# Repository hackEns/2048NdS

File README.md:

Nuit des Sciences 2014
======================

Codes, schematics etc. pour l'installation de LEDs (montage Ledhill) pour la Nuit des Sciences 2014 à l'Ens.

# Structure

* `frontend/`: web interface for playing, customized 2048 game to be used as a controller for the game server.
* `leds/`: code running on the ATmega on the LEDs PCB.
* `pc_control/`: python scripts to send instructions to the LEDs.
* `tests/`: various tests files for both the PCBs and the Serial comm in Python.

# Usage

* Launch `test_order.py` in the `tests` folder, to get the correct order in which LEDs should be controlled.
* Put the output of the previous command in the `get_linear_led_number` function in `pc_control/game.py` line 98 to set the correct order for the LEDs.
* Set the correct controller at the top of `pc_control/game.py`.
* Launch `leds_server.py` in the `pc_control` folder, on the computer connected to the LEDs using a USB FTDI cable. Pass the device `/dev/ttyUSB*` used to communicate with the LEDs as argument.
* Launch `game.py` in the `pc_control` folder passing it the server ip address as first argument. This can be launched on any computer as long as it can communicate with the previous one _via_ the port 4242 (or any other port, if you update the files `game.py` and `leds_server.py` accordingly).
* You are ready to go.

# License

All the source codes, unless explicitly specified otherwise are under the following license:

```
/*
 * --------------------------------------------------------------------------------
 * "THE NO-ALCOHOL BEER-WARE LICENSE" (Revision 42):
 * Phyks (webmaster@phyks.me) wrote or updated these files for hackEns. As long
 * as you retain this notice you can do whatever you want with this stuff
 * (and you can also do whatever you want with this stuff without retaining it,
 * but that's not cool...).
 *
 * If we meet some day, and you think this stuff is worth it, you can buy us a
 * <del>beer</del> soda in return.
 *                                                              Phyks for hackEns
 * ---------------------------------------------------------------------------------
 */
 ```

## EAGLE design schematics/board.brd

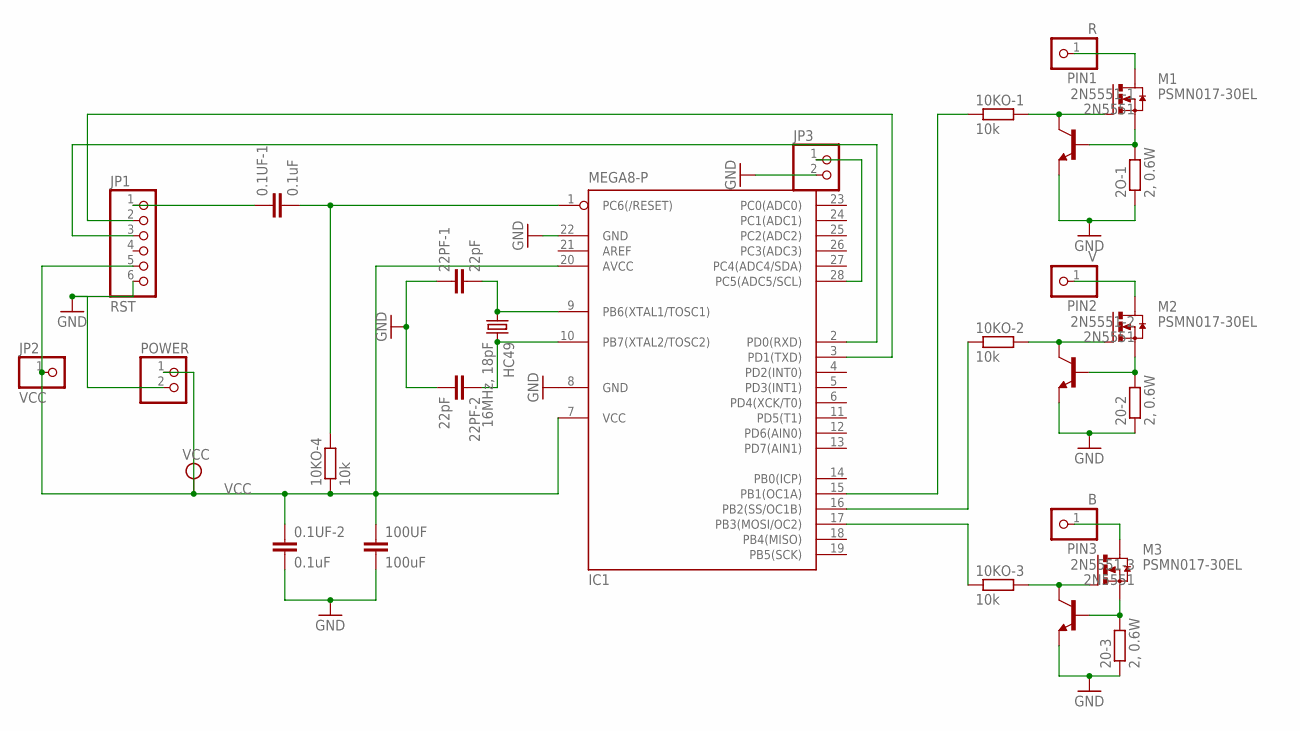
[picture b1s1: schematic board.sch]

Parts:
0.1UF-1, 0.1UF-2: 0.1uF; C025-030X050
2N5551-1, 2N5551-2, 2N5551-3: 2N5551; TO92-CBE
2O-1, 20-2, 20-3: 2, 0.6W; 0309V
10KO-1, 10KO-2, 10KO-3, 10KO-4: 10k; 0207/2V
22PF-1, 22PF-2: 22pF; C025-030X050
100UF: 100uF; C025-050X050
HC49: 16MHz, 18pF; HC49/S
IC1: MEGA8-P; DIL28-3
JP1: RST; 1X06
JP2: VCC; 1X01
JP3: PINHD-1X2; 1X02
M1, M2, M3: PSMN017-30EL; TO262-V
PIN1: R; 1X01
PIN2: V; 1X01
PIN3: B; 1X01
POWER: PINHD-1X2; 1X02

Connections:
GND: 0.1UF-2.2, 2N5551-1.E, 2N5551-2.E, 2N5551-3.E, 2O-1.1, 20-2.1, 20-3.1, 22PF-1.1, 22PF-2.2, 100UF.2, IC1.8 (GND), IC1.22 (GND), JP1.6, JP3.2, POWER.2
unnamed: 22PF-1.2, HC49.1, IC1.9 (PB6(XTAL1/TOSC1))
unnamed: 22PF-2.1, HC49.2, IC1.10 (PB7(XTAL2/TOSC2))
unnamed: 0.1UF-1.1, JP1.1
unnamed: 2N5551-2.C, 10KO-2.2, M2.1 (G)
unnamed: 0.1UF-1.2, 10KO-4.2, IC1.1 (PC6(/RESET))
unnamed: 2N5551-1.C, 10KO-1.2, M1.1 (G)
unnamed: 2N5551-2.B, 20-2.2, M2.3 (S)
unnamed: 2N5551-1.B, 2O-1.2, M1.3 (S)
unnamed: IC1.3 (PD1(TXD)), JP1.2
unnamed: 2N5551-3.C, 10KO-3.2, M3.1 (G)
unnamed: 2N5551-3.B, 20-3.2, M3.3 (S)
unnamed: IC1.2 (PD0(RXD)), JP1.3
unnamed: 10KO-1.1, IC1.15 (PB1(OC1A))
unnamed: 10KO-2.1, IC1.16 (PB2(SS/OC1B))
unnamed: 10KO-3.1, IC1.17 (PB3(MOSI/OC2))
unnamed: M1.2 (D), PIN1.1
unnamed: M2.2 (D), PIN2.1
unnamed: M3.2 (D), PIN3.1
unnamed: IC1.28 (PC5(ADC5/SCL)), JP3.1
VCC: 0.1UF-2.1, 10KO-4.1, 100UF.1, IC1.7 (VCC), IC1.20 (AVCC), JP1.5, JP2.1, POWER.1

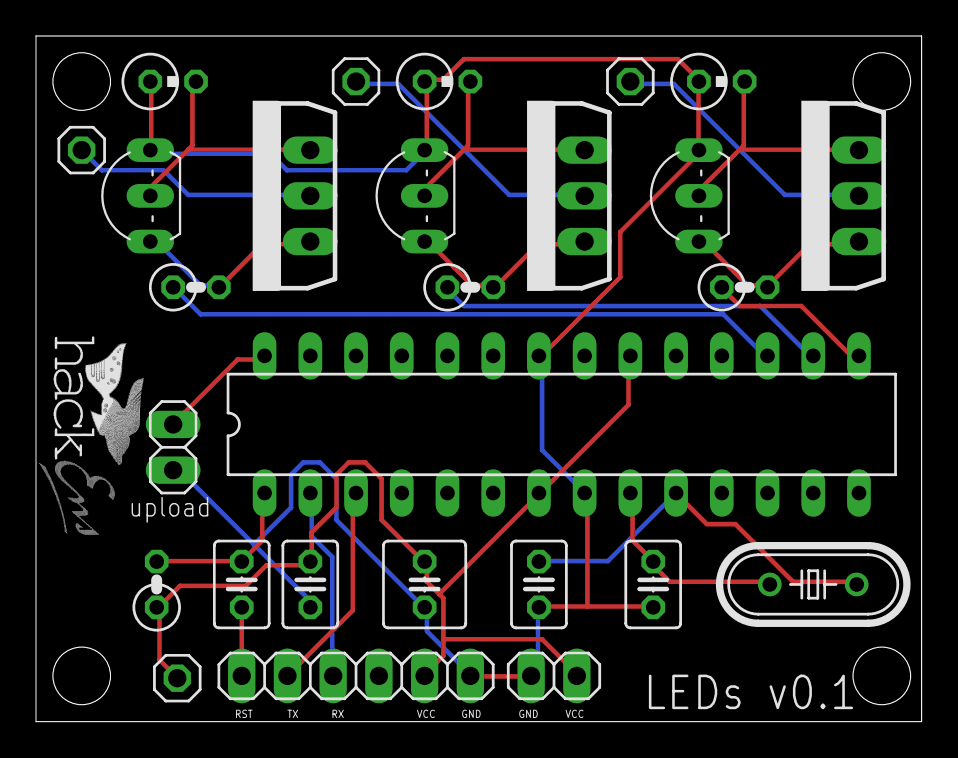
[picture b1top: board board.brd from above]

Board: 2 copper layers, 49.2 x 38.1 mm, 28 parts (0 on the bottom side), 21 nets.

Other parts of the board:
U$1: HACKENS-LOGO

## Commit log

2014-05-19 3x3 + updated layout
2014-05-19 Updated license
2014-05-19 Cleaned repo
2014-05-20 * Code des LEDs * Début du code de contrôle
2014-05-20 Control class
2014-05-22 LED control
2014-05-22 README
2014-05-22 2048 board class
2014-05-22 Complete structure
2014-05-24 LED server should be ok
    Code is composed of two modules :
    * A LED server which receive instructions and forward them to the LEDs
    * A game server which handles the gaming and sends instructions
    accordingly to the LED server.
2014-05-24 Updating game server
2014-05-25 Game server + high scores
2014-05-25 Game server + LED server improved
    * Bugfixes
    TODO : get_diff not working + error in send_colors
2014-05-25 LED server working
2014-05-25 Game working
2014-05-25 README, doc and LICENSE
2014-05-26 README + License
2014-05-26 PEP8 + requests error handling
2014-05-27 Web controller
2014-05-27 Frontend web controller
2014-05-27 Web controller working
2014-05-29 More robust webcontroller
2014-05-29 Controller for the accelerometer app on smartphone
2014-06-02 Default port pour acceleromètre
2014-06-02 Added predefined colors
2014-06-02 Basic visualizer to test anims
2014-06-02 Created a static code for the LED on 45 rue d'Ulm
2014-06-02 Readability
2014-06-03 Visualizer updated
2014-06-03 No threading to respect timing
2014-06-03 Win and lose animations
2014-06-05 Typo in colors
2014-06-05 Animations pour les LEDs du 45
2014-06-05 Animations 45 testées
2014-06-05 Update colors
2014-06-05 Bugfixes
2014-06-05 Bugfix in static leds code
2014-06-05 Bugfix in 45 + test_correction
2014-06-05 Bugfix in test serial
2014-06-05 Rebug fix in test_serial
2014-06-06 Script pour corriger les LEDs
2014-06-06 Position updated
2014-06-06 Bugfix in game
2014-06-06 Updated corrections for the LEDs
2014-06-06 Port 22, port 4242 blocked
2014-06-06 User friendly game.py for controller
2014-06-06 Ordre des LEDs
2014-06-06 Joystick controller, UNTESTED
2014-06-06 Controllers updated
2014-06-06 Bugfixes in game
2014-06-06 Nick selection backend
2014-06-06 Nick selection frontend
2014-06-06 Mauvais path
2014-06-06 Fix numerotation des leds
2014-06-06 update cozy
2014-06-06 Update debug
2014-06-06 Debug FUCKING LIST MUTABLE en python
2014-06-06 Bugfix stupide
2014-06-06 Dégage, le joystick !
2014-06-06 Mauvais ordre pour l'envoi de couleurs
2014-06-06 Solarized colors
2014-06-06 Accelero
2014-06-06 Animations de fin
2014-06-06 Shadowing
2014-06-06 Typage correct ?
2014-06-06 KeyError
2014-06-06 Change back red
2014-06-06 High scores
2014-06-06 IP accelero
2014-06-06 debug
2014-06-06 accelero controller
2014-06-06 Fix green
2014-06-06 frontend updated
2014-06-06 Debug beautiful
2014-06-06 nice debug + clear
2014-06-06 Nice debug
2014-06-06 High score
2014-06-06 Brown --> red
2014-06-06 joli debug
2014-06-06 Fading corrigé
2014-06-06 Pause avant anim
2014-06-06 Tile maximum
2014-06-06 Bad controller
2014-06-06 Change the blue color code.
2014-06-06 Better debug output.
2014-06-06 Shorter dark duration on lose/win anim
2014-06-06 Correct output debug.
2014-06-06 nick à la fin
2014-06-06 Anim de fin
2014-09-25 Add a simple test for checking LEDs order
2014-09-26 Add link to android app
2014-10-07 Add usage instructions in README
2014-10-24 EAGLE schematics (WIP)
2014-10-24 Ajoute alim & logo sur la PCB
2014-10-24 Bigger logo
2014-10-24 Ajout pins upload
2014-10-24 Connecte AVCC et VCC
    D'après la datasheet atmel
    (http://www.farnell.com/datasheets/1698185.pdf )
